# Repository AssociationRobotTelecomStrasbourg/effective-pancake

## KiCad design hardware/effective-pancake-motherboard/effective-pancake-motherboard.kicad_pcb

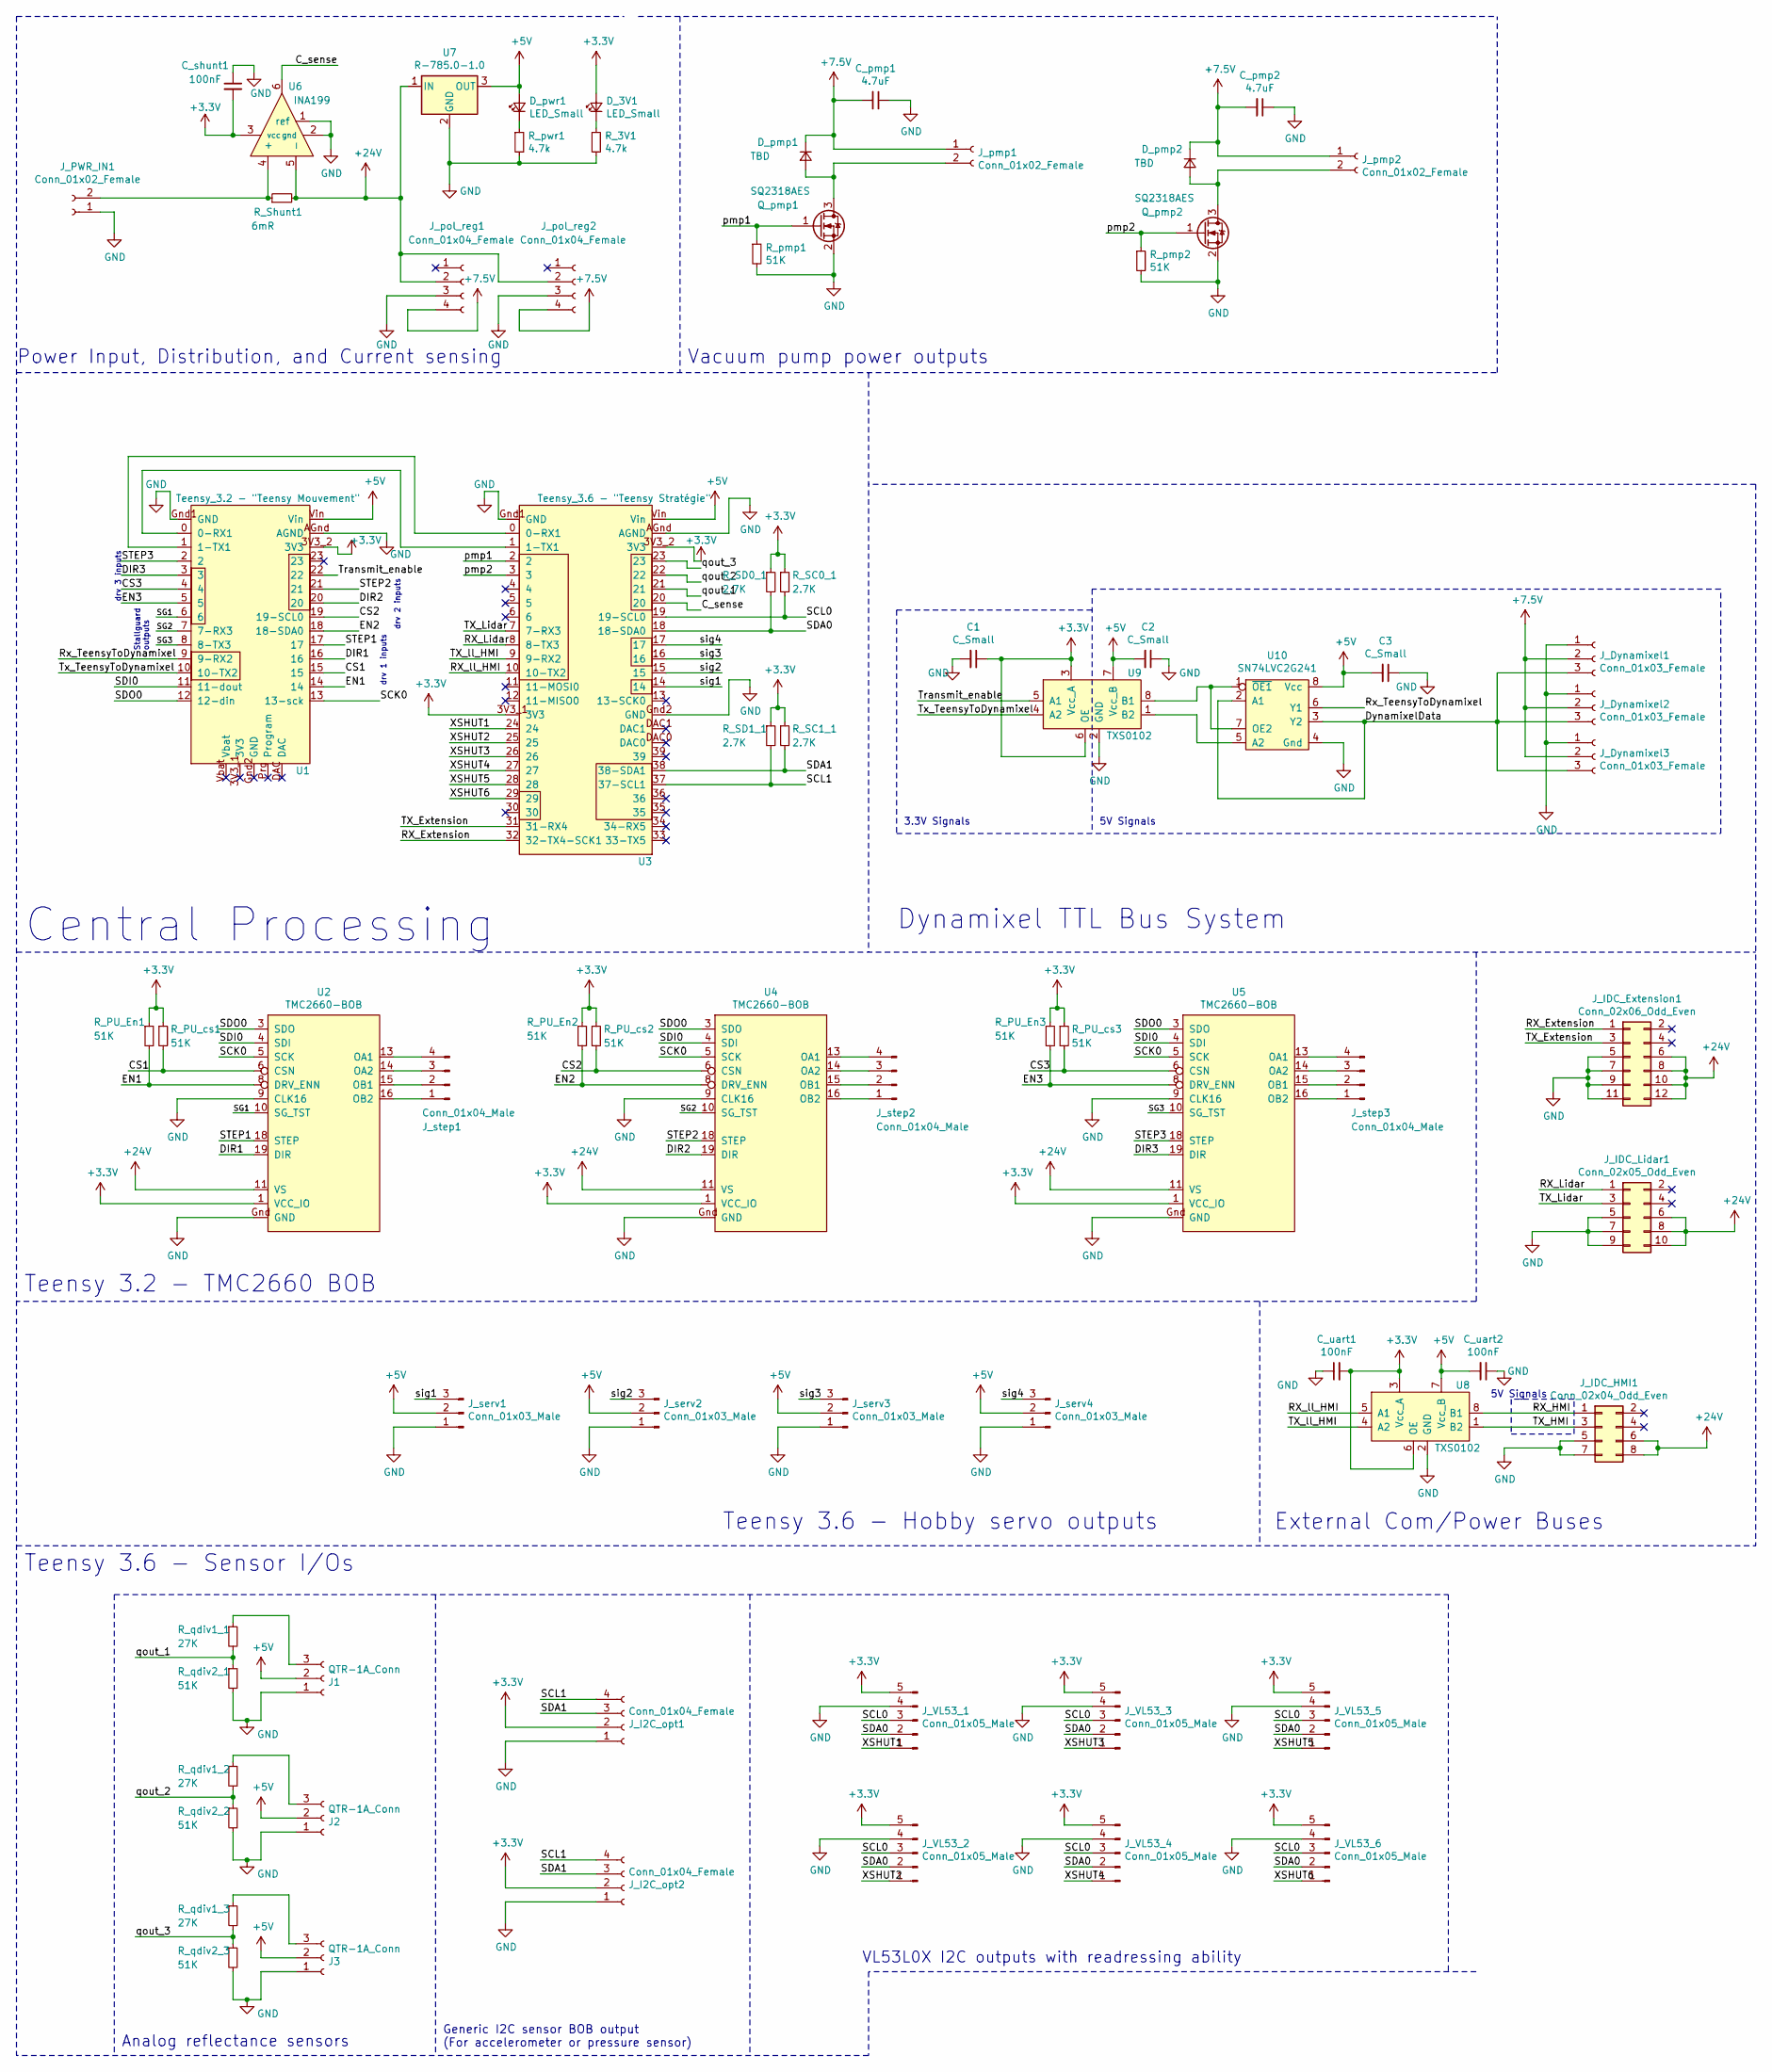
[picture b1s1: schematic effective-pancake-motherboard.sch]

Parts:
C1, C2, C3: C_Small; C_0805_2012Metric_Pad1.15x1.40mm_HandSolder
C_pmp1, C_pmp2: 4.7uF; C_Radial_D4.0mm_H7.0mm_P1.50mm
C_shunt1: 100nF; C_0805_2012Metric_Pad1.15x1.40mm_HandSolder
C_uart1, C_uart2: 100nF; C_0805_2012Metric_Pad1.15x1.40mm_HandSolder
D_3V1: LED_Small; LED_1206_3216Metric_Castellated
D_pmp1, D_pmp2: TBD; D_1206_3216Metric
D_pwr1: LED_Small; LED_1206_3216Metric_Castellated
J1, J2, J3: QTR-1A_Conn; PinHeader_1x03_P2.54mm_Vertical
J_Dynamixel1, J_Dynamixel2, J_Dynamixel3: Conn_01x03_Female; Molex_Micro-Latch_53253-0370_1x03_P2.00mm_Vertical
J_I2C_opt1, J_I2C_opt2: Conn_01x04_Female; PinSocket_1x04_P2.54mm_Vertical
J_IDC_Extension1: Conn_02x06_Odd_Even; IDC-Header_2x06_P2.54mm_Vertical
J_IDC_HMI1: Conn_02x04_Odd_Even; IDC-Header_2x04_P2.54mm_Vertical
J_IDC_Lidar1: Conn_02x05_Odd_Even; IDC-Header_2x05_P2.54mm_Vertical
J_PWR_IN1: Conn_01x02_Female; PhoenixContact_MC_1,5_2-G-5.08_1x02_P5.08mm_Horizontal
J_VL53_1, J_VL53_2, J_VL53_3, J_VL53_4, J_VL53_5, J_VL53_6: Conn_01x05_Male; PinSocket_1x05_P2.54mm_Vertical
J_pmp1, J_pmp2: Conn_01x02_Female; JST_XH_B2B-XH-A_1x02_P2.50mm_Vertical
J_pol_reg1, J_pol_reg2: Conn_01x04_Female; PinSocket_1x04_P2.54mm_Vertical
J_serv1, J_serv2, J_serv3, J_serv4: Conn_01x03_Male; PinHeader_1x03_P2.54mm_Vertical
J_step1, J_step2, J_step3: Conn_01x04_Male; PinHeader_1x04_P2.54mm_Vertical
Q_pmp1, Q_pmp2: SQ2318AES; SOT-23
R_3V1: 4.7k; R_0805_2012Metric_Pad1.15x1.40mm_HandSolder
R_PU_En1, R_PU_En2, R_PU_En3: 51K; R_0805_2012Metric_Pad1.15x1.40mm_HandSolder
R_PU_cs1, R_PU_cs2, R_PU_cs3: 51K; R_0805_2012Metric_Pad1.15x1.40mm_HandSolder
R_SC0_1, R_SC1_1: 2.7K; R_0805_2012Metric_Pad1.15x1.40mm_HandSolder
R_SD0_1, R_SD1_1: 2.7K; R_0805_2012Metric_Pad1.15x1.40mm_HandSolder
R_Shunt1: 6mR; R_1206_3216Metric_Pad1.42x1.75mm_HandSolder
R_pmp1, R_pmp2: 51K; R_0805_2012Metric_Pad1.15x1.40mm_HandSolder
R_pwr1: 4.7k; R_0805_2012Metric_Pad1.15x1.40mm_HandSolder
R_qdiv1_1, R_qdiv1_2, R_qdiv1_3: 27K; R_0805_2012Metric_Pad1.15x1.40mm_HandSolder
R_qdiv2_1, R_qdiv2_2, R_qdiv2_3: 51K; R_0805_2012Metric_Pad1.15x1.40mm_HandSolder
U1: Teensy_3.2 - \"Teensy Mouvement\"; Teensy_3.2
U2, U4, U5: TMC2660-BOB
U3: Teensy_3.6 - \"Teensy Stratégie\"; Teensy_3.6
U6: INA199; Texas_R-PDSO-G6
U7: R-785.0-1.0; Converter_DCDC_RECOM_R-78E-0.5_THT
U8, U9: TXS0102; PDSO-G8
U10: SN74LVC2G241; PDSO-G8

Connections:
+3V3: C1.1, C_shunt1.2, C_uart1.2, D_3V1.2 (A), J_I2C_opt1.2, J_I2C_opt2.2, J_VL53_1.5, J_VL53_2.5, J_VL53_3.5, J_VL53_4.5, J_VL53_5.5, J_VL53_6.5, R_PU_En1.1, R_PU_En2.1, R_PU_En3.1, R_PU_cs1.1, R_PU_cs2.1, R_PU_cs3.1, R_SC0_1.1, R_SC1_1.1, R_SD0_1.1, R_SD1_1.1, U1.3V3_2 (3V3), U2.1 (VCC_IO), U3.3V3_1 (3V3), U3.3V3_2 (3V3), U4.1 (VCC_IO), U5.1 (VCC_IO), U6.3 (vcc), U8.3 (Vcc_A), U8.6 (OE), U9.3 (Vcc_A), U9.6 (OE)
+5V: C2.2, C3.2, C_uart2.2, D_pwr1.2 (A), J1.2, J2.2, J3.2, J_serv1.2, J_serv2.2, J_serv3.2, J_serv4.2, U1.Vin, U3.Vin, U7.3 (OUT), U8.7 (Vcc_B), U9.7 (Vcc_B), U10.8 (Vcc)
+7.5V: C_pmp1.2, C_pmp2.2, D_pmp1.1 (K), D_pmp2.1 (K), J_Dynamixel1.2, J_Dynamixel2.2, J_Dynamixel3.2, J_pmp1.1, J_pmp2.1, J_pol_reg1.4, J_pol_reg2.4
+24V: J_IDC_Extension1.6, J_IDC_Extension1.8, J_IDC_Extension1.10, J_IDC_Extension1.12, J_IDC_HMI1.6, J_IDC_HMI1.8, J_IDC_Lidar1.6, J_IDC_Lidar1.8, J_IDC_Lidar1.10, J_pol_reg1.2, J_pol_reg2.2, R_Shunt1.2, U2.11 (VS), U4.11 (VS), U5.11 (VS), U6.5 (-), U7.1 (IN)
/CS1: R_PU_cs1.2, U1.15, U2.6 (CSN)
/CS2: R_PU_cs2.2, U1.19 (19-SCL0), U4.6 (CSN)
/CS3: R_PU_cs3.2, U1.4, U5.6 (CSN)
/C_sense: U3.20, U6.6
/DIR1: U1.16, U2.19 (DIR)
/DIR2: U1.20, U4.19 (DIR)
/DIR3: U1.3, U5.19 (DIR)
/DynamixelData: J_Dynamixel1.3, J_Dynamixel2.3, J_Dynamixel3.3, U10.2 (A1), U10.3 (Y2)
/EN1: R_PU_En1.2, U1.14, U2.8 (DRV_ENN)
/EN2: R_PU_En2.2, U1.18 (18-SDA0), U4.8 (DRV_ENN)
/EN3: R_PU_En3.2, U1.5, U5.8 (DRV_ENN)
/RX_Extension: J_IDC_Extension1.1, U3.32 (32-TX4-SCK1)
/RX_HMI: J_IDC_HMI1.1, U8.8 (B1)
/RX_Lidar: J_IDC_Lidar1.1, U3.8 (8-TX3)
/RX_ll_HMI: U3.10 (10-TX2), U8.5 (A1)
/Rx_TeensyToDynamixel: U1.9 (9-RX2), U10.6 (Y1)
/SCK0: U1.13 (13-sck), U2.5 (SCK), U4.5 (SCK), U5.5 (SCK)
/SCL0: J_VL53_1.3, J_VL53_2.3, J_VL53_3.3, J_VL53_4.3, J_VL53_5.3, J_VL53_6.3, R_SC0_1.2, U3.19 (19-SCL0)
/SCL1: J_I2C_opt1.4, J_I2C_opt2.4, R_SD1_1.2, U3.37 (37-SCL1)
/SDA0: J_VL53_1.2, J_VL53_2.2, J_VL53_3.2, J_VL53_4.2, J_VL53_5.2, J_VL53_6.2, R_SD0_1.2, U3.18 (18-SDA0)
/SDA1: J_I2C_opt1.3, J_I2C_opt2.3, R_SC1_1.2, U3.38 (38-SDA1)
/SDI0: U1.11 (11-dout), U2.4 (SDI), U4.4 (SDI), U5.4 (SDI)
/SDO0: U1.12 (12-din), U2.3 (SDO), U4.3 (SDO), U5.3 (SDO)
/SG1: U1.6, U2.10 (SG_TST)
/SG2: U1.7 (7-RX3), U4.10 (SG_TST)
/SG3: U1.8 (8-TX3), U5.10 (SG_TST)
/STEP1: U1.17, U2.18 (STEP)
/STEP2: U1.21, U4.18 (STEP)
/STEP3: U1.2, U5.18 (STEP)
/TX_Extension: J_IDC_Extension1.3, U3.31 (31-RX4)
/TX_HMI: J_IDC_HMI1.3, U8.1 (B2)
/TX_Lidar: J_IDC_Lidar1.3, U3.7 (7-RX3)
/TX_ll_HMI: U3.9 (9-RX2), U8.4 (A2)
/Transmit_enable: U1.22, U9.5 (A1)
/Tx_TeensyToDynamixel: U1.10 (10-TX2), U9.4 (A2)
/XSHUT1: J_VL53_1.1, U3.24
/XSHUT2: J_VL53_2.1, U3.25
/XSHUT3: J_VL53_3.1, U3.26
/XSHUT4: J_VL53_4.1, U3.27
/XSHUT5: J_VL53_5.1, U3.28
/XSHUT6: J_VL53_6.1, U3.29
/pmp1: Q_pmp1.1 (G), R_pmp1.1, U3.2
/pmp2: Q_pmp2.1 (G), R_pmp2.1, U3.3
/qout_1: R_qdiv1_1.2, R_qdiv2_1.1, U3.21
/qout_2: R_qdiv1_2.2, R_qdiv2_2.1, U3.22
/qout_3: R_qdiv1_3.2, R_qdiv2_3.1, U3.23
/sig1: J_serv1.3, U3.14
/sig2: J_serv2.3, U3.15
/sig3: J_serv3.3, U3.16
/sig4: J_serv4.3, U3.17
GND: C1.2, C2.1, C3.1, C_pmp1.1, C_pmp2.1, C_shunt1.1, C_uart1.1, C_uart2.1, J1.1, J2.1, J3.1, J_Dynamixel1.1, J_Dynamixel2.1, J_Dynamixel3.1, J_I2C_opt1.1, J_I2C_opt2.1, J_IDC_Extension1.5, J_IDC_Extension1.7, J_IDC_Extension1.9, J_IDC_Extension1.11, J_IDC_HMI1.5, J_IDC_HMI1.7, J_IDC_Lidar1.5, J_IDC_Lidar1.7, J_IDC_Lidar1.9, J_PWR_IN1.1, J_VL53_1.4, J_VL53_2.4, J_VL53_3.4, J_VL53_4.4, J_VL53_5.4, J_VL53_6.4, J_pol_reg1.3, J_pol_reg2.3, J_serv1.1, J_serv2.1, J_serv3.1, J_serv4.1, Q_pmp1.2 (S), Q_pmp2.2 (S), R_3V1.2, R_pmp1.2, R_pmp2.2, R_pwr1.2, R_qdiv2_1.2, R_qdiv2_2.2, R_qdiv2_3.2, U1.AGnd (AGND), U1.Gnd1 (GND), U2.9 (CLK16), U2.Gnd (GND), U3.AGnd (AGND), U3.Gnd1 (GND), U3.Gnd2 (GND), U4.9 (CLK16), U4.Gnd (GND), U5.9 (CLK16), U5.Gnd (GND), U6.1 (ref), U6.2 (gnd), U7.2 (GND), U8.2 (GND), U9.2 (GND), U10.4 (Gnd)
unnamed: D_3V1.1 (K), R_3V1.1
unnamed: D_pmp1.2 (A), J_pmp1.2, Q_pmp1.3 (D)
unnamed: D_pmp2.2 (A), J_pmp2.2, Q_pmp2.3 (D)
unnamed: D_pwr1.1 (K), R_pwr1.1
unnamed: J1.3, R_qdiv1_1.1
unnamed: J2.3, R_qdiv1_2.1
unnamed: J3.3, R_qdiv1_3.1
unnamed: J_PWR_IN1.2, R_Shunt1.1, U6.4 (+)
unnamed: J_step1.1, U2.16 (OB2)
unnamed: J_step1.2, U2.15 (OB1)
unnamed: J_step1.3, U2.14 (OA2)
unnamed: J_step1.4, U2.13 (OA1)
unnamed: J_step2.1, U4.16 (OB2)
unnamed: J_step2.2, U4.15 (OB1)
unnamed: J_step2.3, U4.14 (OA2)
unnamed: J_step2.4, U4.13 (OA1)
unnamed: J_step3.1, U5.16 (OB2)
unnamed: J_step3.2, U5.15 (OB1)
unnamed: J_step3.3, U5.14 (OA2)
unnamed: J_step3.4, U5.13 (OA1)
unnamed: U1.0 (0-RX1), U3.1 (1-TX1)
unnamed: U1.1 (1-TX1), U3.0 (0-RX1)
unnamed: U9.8 (B1), U10.1 (~OE1), U10.7 (OE2)
unnamed: U9.1 (B2), U10.5 (A2)

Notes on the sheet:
5V Signals
drv 1 inputs
drv 2 inputs
drv 3 inputs
Stallguard outputs
Teensy 3.2 - TMC2660 BOB
Teensy 3.6 - Sensor I/Os
Analog reflectance sensors
Generic I2C sensor BOB output (For accelerometer or pressure sensor)
VL53L0X I2C outputs with readressing ability
Teensy 3.6 - Hobby servo outputs
Central Processing
Power Input, Distribution, and Current sensing
External Com/Power Buses
Vacuum pump power outputs
Dynamixel TTL Bus System
3.3V Signals

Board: 2 copper layers, 74 parts (0 on the bottom side), 79 nets, no tracks yet.

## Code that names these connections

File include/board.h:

#ifndef BOARD_H
#define BOARD_H

#include <Arduino.h>

// Hardware Serial port 1, connected to ESP01
#define RX1 0
#define TX1 1

// Tactile Switch input
#define BTN 23

// Pins for Driver 1, 2 and 3
#define DIR1 8
#define STEP1 9
#define EN1 10

#define DIR2 5
#define STEP2 6
#define EN2 7

#define DIR3 2
#define STEP3 3
#define EN3 4

void waitForButton();

#endif

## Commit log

2019-12-12 Added TeensyStep lib
2019-12-12 Added Locomotion
2019-12-13 Added setSpeeds and waitForButton
2019-12-19 Added setRobotSpeeds()
2020-01-01 hardware file structure & ongoing CAD
2020-01-04 Finished schematics, fp association, and verifications.
